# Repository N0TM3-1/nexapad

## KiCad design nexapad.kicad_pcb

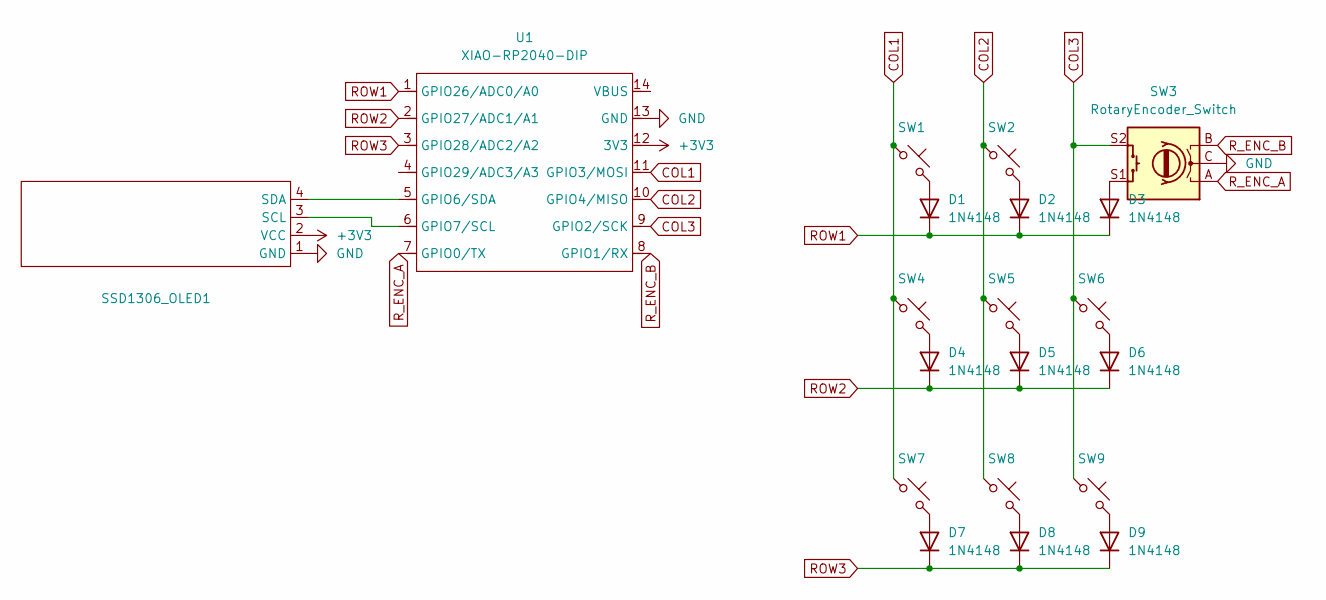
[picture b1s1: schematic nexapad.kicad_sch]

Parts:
D1, D2, D3, D4, D5, D6, D7, D8, D9: 1N4148; D_DO-35_SOD27_P7.62mm_Horizontal
SSD1306_OLED1: SSD1306-0.91-OLED
SW1, SW2, SW4, SW5, SW6, SW7, SW8, SW9: SW_Push_45deg; SW_Cherry_MX_1.00u_PCB
SW3: RotaryEncoder_Switch; RotaryEncoder_Alps_EC11E-Switch_Vertical_H20mm
U1: XIAO-RP2040-DIP

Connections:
+3V3: SSD1306_OLED1.2 (VCC), U1.12 (3V3)
COL1: SW1.1, SW4.1, SW7.1, U1.11 (GPIO3/MOSI)
COL2: SW2.1, SW5.1, SW8.1, U1.10 (GPIO4/MISO)
COL3: SW3.S2, SW6.1, SW9.1, U1.9 (GPIO2/SCK)
GND: SSD1306_OLED1.1 (GND), SW3.C, U1.13 (GND)
unnamed: D1.2 (A), SW1.2
unnamed: D2.2 (A), SW2.2
unnamed: D3.2 (A), SW3.S1
unnamed: D4.2 (A), SW4.2
unnamed: D5.2 (A), SW5.2
unnamed: D6.2 (A), SW6.2
unnamed: D7.2 (A), SW7.2
unnamed: D8.2 (A), SW8.2
unnamed: D9.2 (A), SW9.2
unnamed: SSD1306_OLED1.3 (SCL), U1.6 (GPIO7/SCL)
unnamed: SSD1306_OLED1.4 (SDA), U1.5 (GPIO6/SDA)
ROW1: D1.1 (K), D2.1 (K), D3.1 (K), U1.1 (GPIO26/ADC0/A0)
ROW2: D4.1 (K), D5.1 (K), D6.1 (K), U1.2 (GPIO27/ADC1/A1)
ROW3: D7.1 (K), D8.1 (K), D9.1 (K), U1.3 (GPIO28/ADC2/A2)
R_ENC_A: SW3.A, U1.7 (GPIO0/TX)
R_ENC_B: SW3.B, U1.8 (GPIO1/RX)

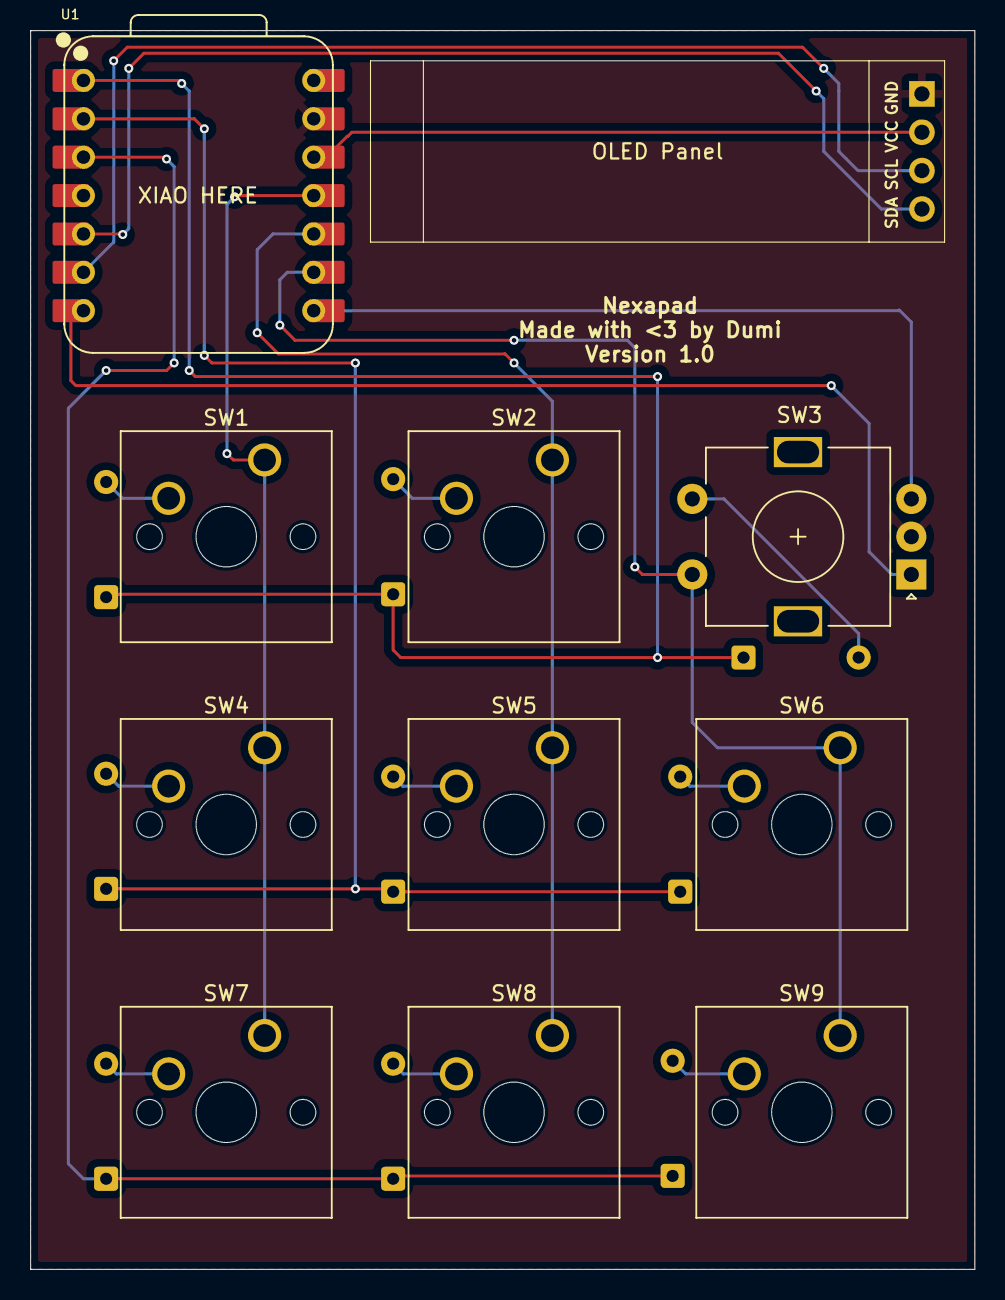
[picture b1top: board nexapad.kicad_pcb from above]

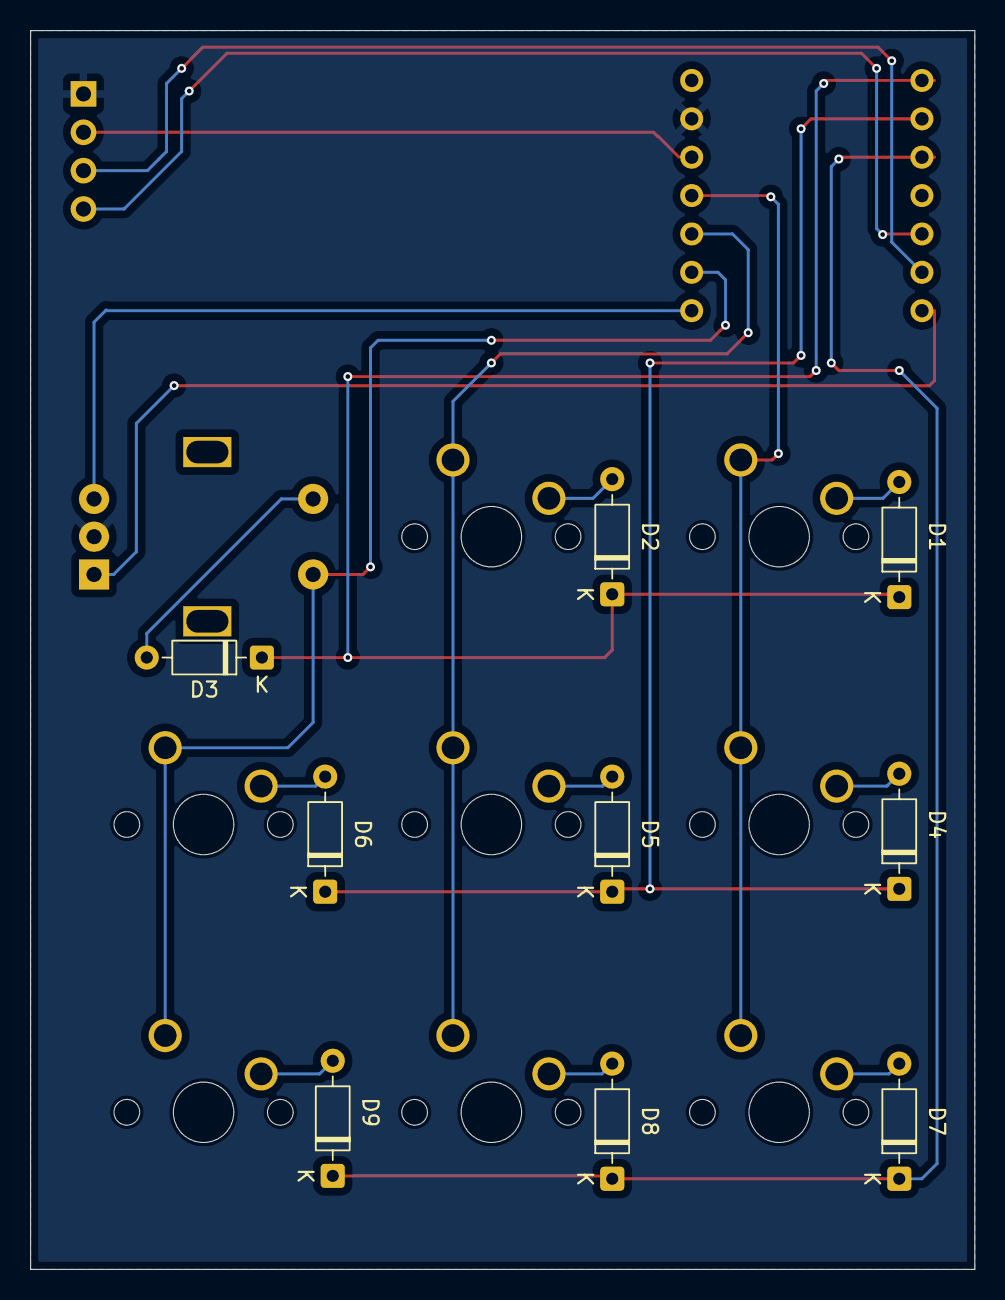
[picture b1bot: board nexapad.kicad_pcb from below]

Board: 2 copper layers, 62.5 x 82.0 mm, 20 parts (9 on the bottom side), 21 nets.

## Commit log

2025-07-10 Finished the PCB
